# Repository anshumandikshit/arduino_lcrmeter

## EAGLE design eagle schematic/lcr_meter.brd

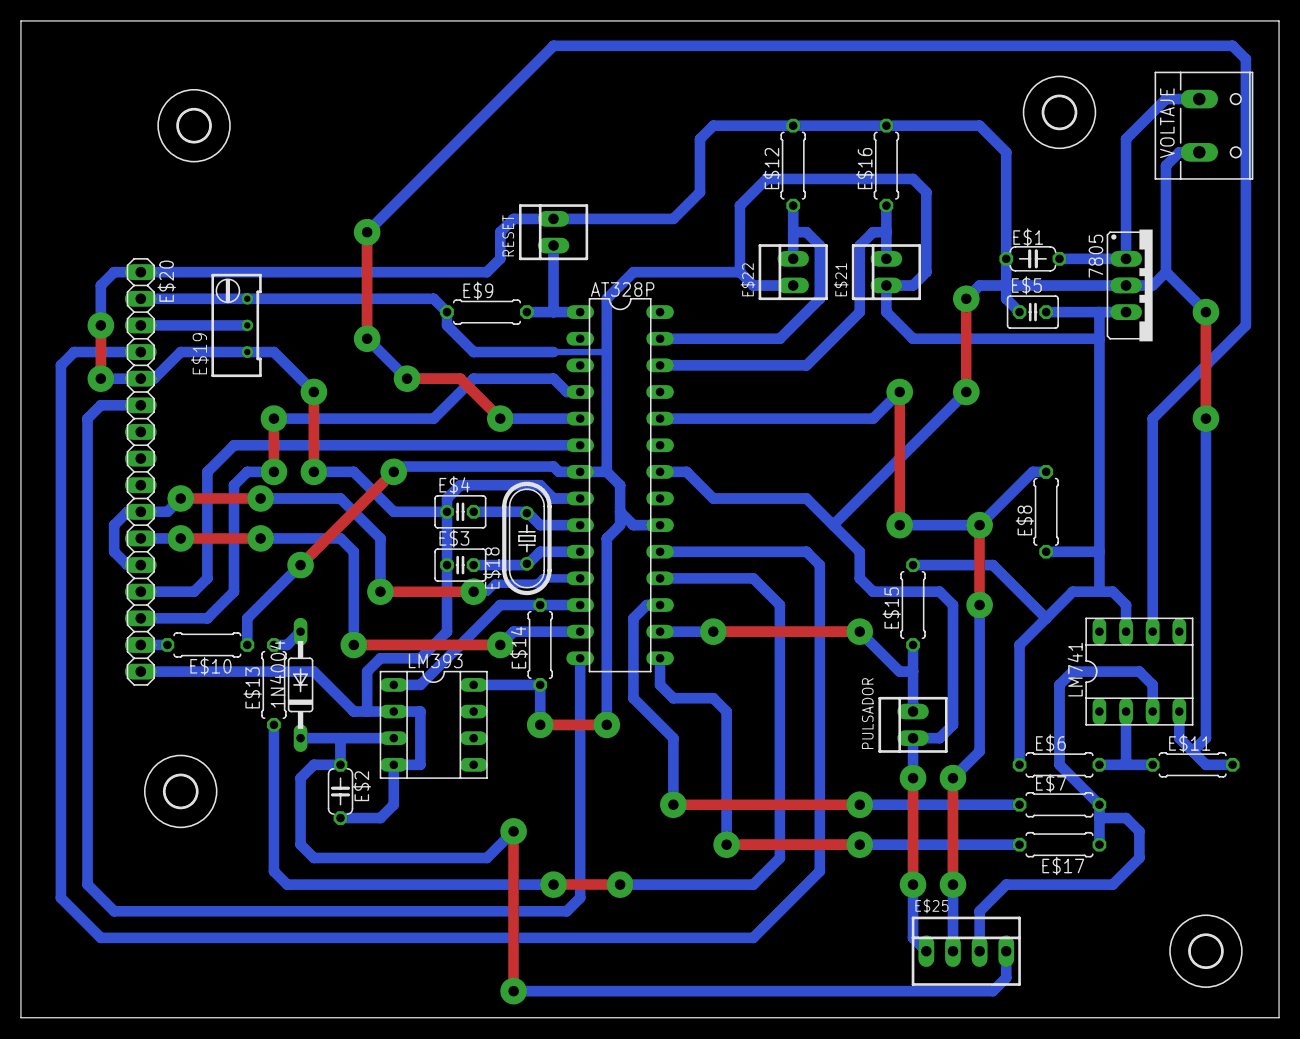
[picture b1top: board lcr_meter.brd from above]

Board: 2 copper layers, 120.0 x 95.1 mm, 35 parts (0 on the bottom side), 28 nets.

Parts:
1N4004: C2992
7805: 78XXS
AT328P: DIL28-3
E$1: 0.33uF; C050-024X044
E$2: 1uF; C050-024X044
E$3, E$4: 22pF; C025-030X050
E$5: 100nF; C025-030X050
E$6, E$8, E$9, E$11, E$12, E$15, E$16: 10k; 0207/7
E$7: 1M; 0207/7
E$10, E$17: 220; 0207/7
E$13: 150; 0207/7
E$14: 330; 0207/7
E$18: 16Mhz; HC49/S
E$19: 10k; RTRIM64W
E$20: 1X16
E$21, E$22: 22-23-2021
E$23, E$24, E$26, E$27: 3,0
E$25: 22-23-2041
LM393, LM741: SOCKET-08
PULSADOR: 22-23-2021
RESET: 22-23-2021
VOLTAJE: W237-132

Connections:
S$1: AT328P.10, E$3.2
S$2: AT328P.9, E$4.2
S$4: AT328P.1, E$9.2, RESET.1
S$5: AT328P.11, E$20.12
S$6: 1N4004.C, E$2.1, E$25.4, LM393.3
S$7: AT328P.18, E$13.1
S$8: AT328P.12, LM393.1
S$9: 1N4004.A, E$13.2
S$10: AT328P.16, E$15.1, PULSADOR.2
S$11: E$19.2, E$20.3
S$12: AT328P.19, E$20.4
S$13: E$10.2, E$20.15
S$14: AT328P.14, E$20.6
S$15: AT328P.6, E$20.13
S$16: AT328P.4, E$20.14
S$17: E$6.2, E$11.1, LM741.2
S$18: AT328P.24, E$8.2, E$25.2
S$19: AT328P.13, E$20.11
S$20: E$17.1, E$25.3, LM741.3
S$21: AT328P.27, E$12.1, E$22.2
S$22: AT328P.8, E$2.2, E$3.1, E$4.1, E$20.16, LM393.2, LM393.4
S$23: AT328P.26, E$16.1, E$21.2
S$24: 7805.OUT, AT328P.7, AT328P.20, E$5.2, E$6.1, E$8.1, E$9.1, E$14.1, E$15.2, E$19.3, E$20.2, E$21.1, E$22.1, LM393.8, LM741.7
S$26: 7805.GND, AT328P.22, E$1.1, E$5.1, E$11.2, E$12.2, E$16.2, E$19.1, E$20.1, E$20.5, E$25.1, LM741.4, PULSADOR.1, RESET.2
S$28: AT328P.15, E$17.2
S$29: AT328P.5, LM741.6
S$31: AT328P.17, E$7.1
S$34: 7805.IN, E$1.2

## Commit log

2017-09-01 lcr meter
    arduino lcr meter
